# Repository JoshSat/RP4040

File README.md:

# RP4040
dual dual core!

two RP2040 on a single carrier board with all pins exposed as pads. LGA 84 needs to be developed and pads are not set in stone and will probably be adjusted to make more space. Flash chips are going to be in side the socket and USB is on the pads with their resistors.

Things to do:
rename componets so there are no skipped numbers

~~~~~~~~~~~~~~~~~~~~~~~~~~~~~~~~~~~~~~~~~~~~~~~~~~~~~~~~~~~~~~~~~~~~~~~~~~~~~~~~~~~~~~~~~~~~~~~~~~~~~~~~~~~~~~~~~~~~~~~~~~~

~~~~~~~~~~~~~~~~~~~~~~~~~~~~~~~~~~~~~~~~~~~~~~~~~~~~~~~~~~~~~~~~~~~~~~~~~~~~~~~~~~~~~~~~~~~~~~~~~~~~~~~~~~~~~~~~~~~~~~~~~~~~~~~

~~~~~~~~~~~~~~~~~~~~~~~~~~~~~~~~~~~~~~~~~~~~~~~~~~~~~~~~~~~~~~~~~~~~~~~~~~~~~~~~~~~~~~~~~~~~~~~~~~~~~~~~~~~~~~~~~~~~~~~~~~~~~~~

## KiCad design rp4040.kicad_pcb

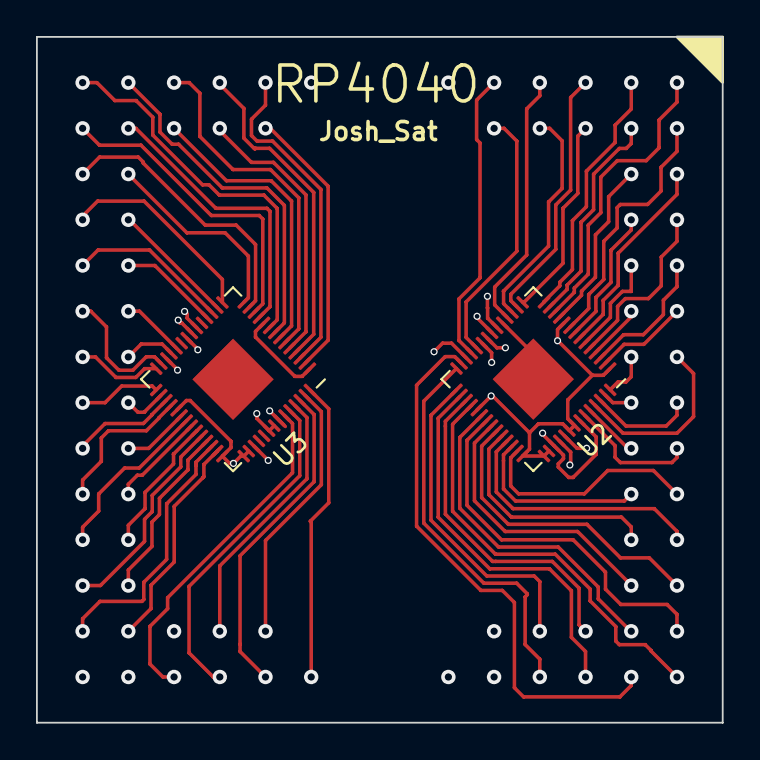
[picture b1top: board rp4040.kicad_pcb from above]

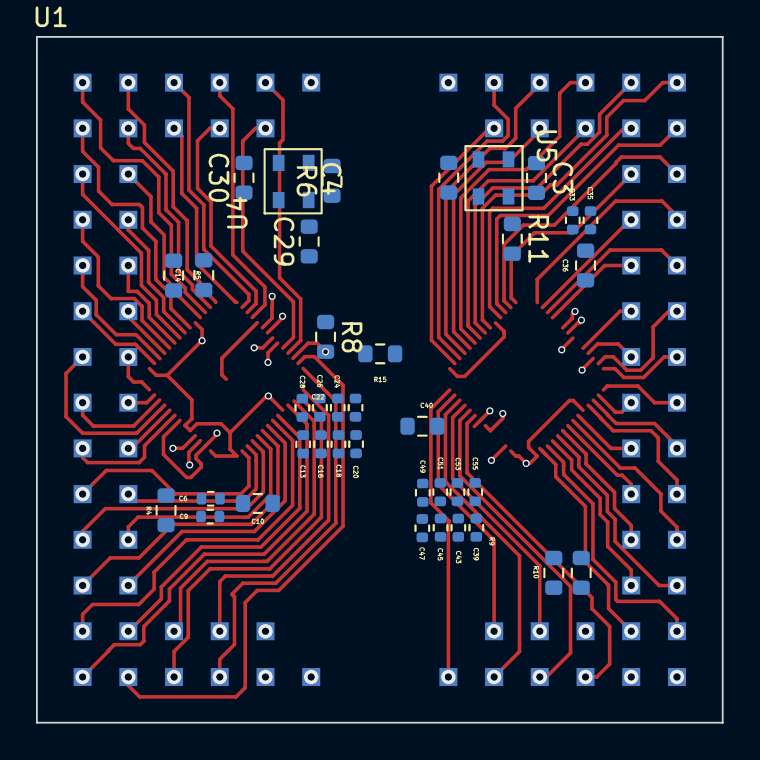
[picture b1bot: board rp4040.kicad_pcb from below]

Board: 2 copper layers, 38.1 x 38.1 mm, 41 parts (39 on the bottom side), 95 nets.

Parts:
C3, C4, C29, C30: 27p; R_0603_1608Metric
C6, C9, C13, C16, C18, C20, C22, C24, C26, C28, C33, C35, C39, C43, C45, C47, C49, C51, C53, C55: 100nf; R_0402_1005Metric
C10, C14, C36, C40: 1uf; R_0603_1608Metric
R4, R5, R9, R10: 27ohm; R_0603_1608Metric
R6, R11: 1k; R_0603_1608Metric
R8, R15: 10k; R_0603_1608Metric
U1: LGA84
U2, U3: RP2040; QFN-56-1EP_7x7mm_P0.4mm_EP3.2x3.2mm
U4, U5: rh100

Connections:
+1V1: C6.1, C9.1, C10.1, C33.1, C35.1, C36.1, U2.23 (DVDD), U2.45 (VREG_VOUT), U2.50 (DVDD), U3.23 (DVDD), U3.45 (VREG_VOUT), U3.50 (DVDD)
+3.3V: C13.1, C14.1, C16.1, C18.1, C20.1, C22.1, C24.1, C26.1, C28.1, C39.1, C40.1, C43.1, C45.1, C47.1, C49.1, C51.1, C53.1, C55.1, R8.1, R15.1, U1.41, U1.46, U2.1 (IOVDD), U2.10 (IOVDD), U2.22 (IOVDD), U2.33 (IOVDD), U2.42 (IOVDD), U2.43 (ADC_AVDD), U2.44 (VREG_IN), U2.48 (USB_VDD), U2.49 (IOVDD), U3.1 (IOVDD), U3.10 (IOVDD), U3.22 (IOVDD), U3.33 (IOVDD), U3.42 (IOVDD), U3.43 (ADC_AVDD), U3.44 (VREG_IN), U3.48 (USB_VDD), U3.49 (IOVDD)
/GPIO0_0: U1.9, U2.2 (GPIO0)
/GPIO0_1: U1.47, U3.2 (GPIO0)
/GPIO1_0: U1.10, U2.3 (GPIO1)
/GPIO1_1: U1.48, U3.3 (GPIO1)
/GPIO2_0: U1.20, U2.4 (GPIO2)
/GPIO2_1: U1.49, U3.4 (GPIO2)
/GPIO3_0: U1.11, U2.5 (GPIO3)
/GPIO3_1: U1.50, U3.5 (GPIO3)
/GPIO4_0: U1.19, U2.6 (GPIO4)
/GPIO4_1: U1.51, U3.6 (GPIO4)
/GPIO5_0: U1.12, U2.7 (GPIO5)
/GPIO5_1: U1.52, U3.7 (GPIO5)
/GPIO6_0: U1.18, U2.8 (GPIO6)
/GPIO6_1: U1.70, U3.8 (GPIO6)
/GPIO7_0: U1.13, U2.9 (GPIO7)
/GPIO7_1: U1.71, U3.9 (GPIO7)
/GPIO8_0: U1.17, U2.11 (GPIO8)
/GPIO8_1: U1.69, U3.11 (GPIO8)
/GPIO9_0: U1.14, U2.12 (GPIO9)
/GPIO9_1: U1.72, U3.12 (GPIO9)
/GPIO10_0: U1.16, U2.13 (GPIO10)
/GPIO10_1: U1.73, U3.13 (GPIO10)
/GPIO11_0: U1.15, U2.14 (GPIO11)
/GPIO11_1: U1.68, U3.14 (GPIO11)
/GPIO12_0: U1.33, U2.15 (GPIO12)
/GPIO12_1: U1.74, U3.15 (GPIO12)
/GPIO13_0: U1.34, U2.16 (GPIO13)
/GPIO13_1: U1.67, U3.16 (GPIO13)
/GPIO14_0: U1.35, U2.17 (GPIO14)
/GPIO14_1: U1.75, U3.17 (GPIO14)
/GPIO15_0: U1.36, U2.18 (GPIO15)
/GPIO15_1: U1.66, U3.18 (GPIO15)
/GPIO16_0: U1.28, U2.27 (GPIO16)
/GPIO16_1: U1.76, U3.27 (GPIO16)
/GPIO17_0: U1.29, U2.28 (GPIO17)
/GPIO17_1: U1.77, U3.28 (GPIO17)
/GPIO18_0: U1.30, U2.29 (GPIO18)
/GPIO18_1: U1.78, U3.29 (GPIO18)
/GPIO19_0: U1.31, U2.30 (GPIO19)
/GPIO19_1: U1.63, U3.30 (GPIO19)
/GPIO20_0: U1.32, U2.31 (GPIO20)
/GPIO20_1: U1.79, U3.31 (GPIO20)
/GPIO21_0: U1.1, U2.32 (GPIO21)
/GPIO21_1: U1.80, U3.32 (GPIO21)
/GPIO22_0: U1.27, U2.34 (GPIO22)
/GPIO22_1: U1.62, U3.34 (GPIO22)
/GPIO23_0: U1.2, U2.35 (GPIO23)
/GPIO23_1: U1.81, U3.35 (GPIO23)
/GPIO24_0: U1.26, U2.36 (GPIO24)
/GPIO24_1: U1.61, U3.36 (GPIO24)
/GPIO25_0: U1.3, U2.37 (GPIO25)
/GPIO25_1: U1.60, U3.37 (GPIO25)
/GPIO26_0: U1.25, U2.38 (GPIO26_ADC0)
/GPIO26_1: U1.82, U3.38 (GPIO26_ADC0)
/GPIO27_0: U1.4, U2.39 (GPIO27_ADC1)
/GPIO27_1: U1.59, U3.39 (GPIO27_ADC1)
/GPIO28_0: U1.24, U2.40 (GPIO28_ADC2)
/GPIO28_1: U1.83, U3.40 (GPIO28_ADC2)
/GPIO29_0: U1.5, U2.41 (GPIO29_ADC3)
/GPIO29_1: U1.58, U3.41 (GPIO29_ADC3)
/QSPISCLK_0: U1.23, U2.52 (QSPI_SCLK)
/QSPISCLK_1: U1.56, U3.52 (QSPI_SCLK)
/QSPISD1_0: U1.22, U2.55 (QSPI_SD1)
/QSPISD1_1: U1.44, U3.55 (QSPI_SD1)
/QSPISD2_0: U1.7, U2.54 (QSPI_SD2)
/QSPISD2_1: U1.43, U3.54 (QSPI_SD2)
/QSPISD3_0: U1.6, U2.51 (QSPI_SD3)
/QSPISD3_1: U1.54, U3.51 (QSPI_SD3)
/QSPISDO_0: U1.8, U2.53 (QSPI_SD0)
/QSPISDO_1: U1.55, U3.53 (QSPI_SD0)
/QSPISS_0: U1.21, U2.56 (QSPI_SS)
/QSPISS_1: U1.45, U3.56 (QSPI_SS)
/SWCLK_0: U1.38, U2.24 (SWCLK)
/SWCLK_1: U1.65, U3.24 (SWCLK)
/SWD_0: U1.37, U2.25 (SWD)
/SWD_1: U1.64, U3.25 (SWD)
/USBDM_0: R5.1, U1.39
/USBDM_1: R10.1, U1.57
/USBDP_0: R4.1, U1.42
/USBDP_1: R9.1, U1.84
GND: C3.1, C4.1, C6.2, C9.2, C10.2, C13.2, C14.2, C16.2, C18.2, C20.2, C22.2, C24.2, C26.2, C28.2, C29.1, C30.1, C33.2, C35.2, C36.2, C39.2, C40.2, C43.2, C45.2, C47.2, C49.2, C51.2, C53.2, C55.2, U1.40, U1.53, U2.19 (TESTEN), U2.57 (GND), U3.19 (TESTEN), U3.57 (GND), U4.1, U4.3, U5.1, U5.3
unnamed: C3.2, U2.20 (XIN), U4.2
unnamed: C4.2, R6.1, U4.4
unnamed: C29.2, U3.20 (XIN), U5.2
unnamed: C30.2, R11.1, U5.4
unnamed: R4.2, U2.47 (USB_DP)
unnamed: R5.2, U2.46 (USB_DM)
unnamed: R6.2, U2.21 (XOUT)
unnamed: R8.2, U2.26 (RUN)
unnamed: R9.2, U3.47 (USB_DP)
unnamed: R10.2, U3.46 (USB_DM)
unnamed: R11.2, U3.21 (XOUT)
unnamed: R15.2, U3.26 (RUN)

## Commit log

2022-12-30 Add files via upload
    unfisnished files
2022-12-30 Add files via upload
    update to progrssion
2022-12-31 31dec22 update
